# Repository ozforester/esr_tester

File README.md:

# In Circuit ESR Tester
batteries 2xAAA<br>
uc stm32f030f4p6 (cmsis)<br>
opamp mcp6001<br>
switch sn74lvc1g3157dvbr<br>
oled ssd1306 (128x32)<br>
sch and pcb (kicad)<br>

Управляемый делитель операционника для тех,<br>
кто решит экспериментировать с измерением<br>
ёмкости (адаптируя частототу шимов под esr)<br>
Пробная директива сдвига на pi/2 между сигналами<br>
(без адаптации) в главном заголовочном файле<br> 
todo проверка конденсатора на кз

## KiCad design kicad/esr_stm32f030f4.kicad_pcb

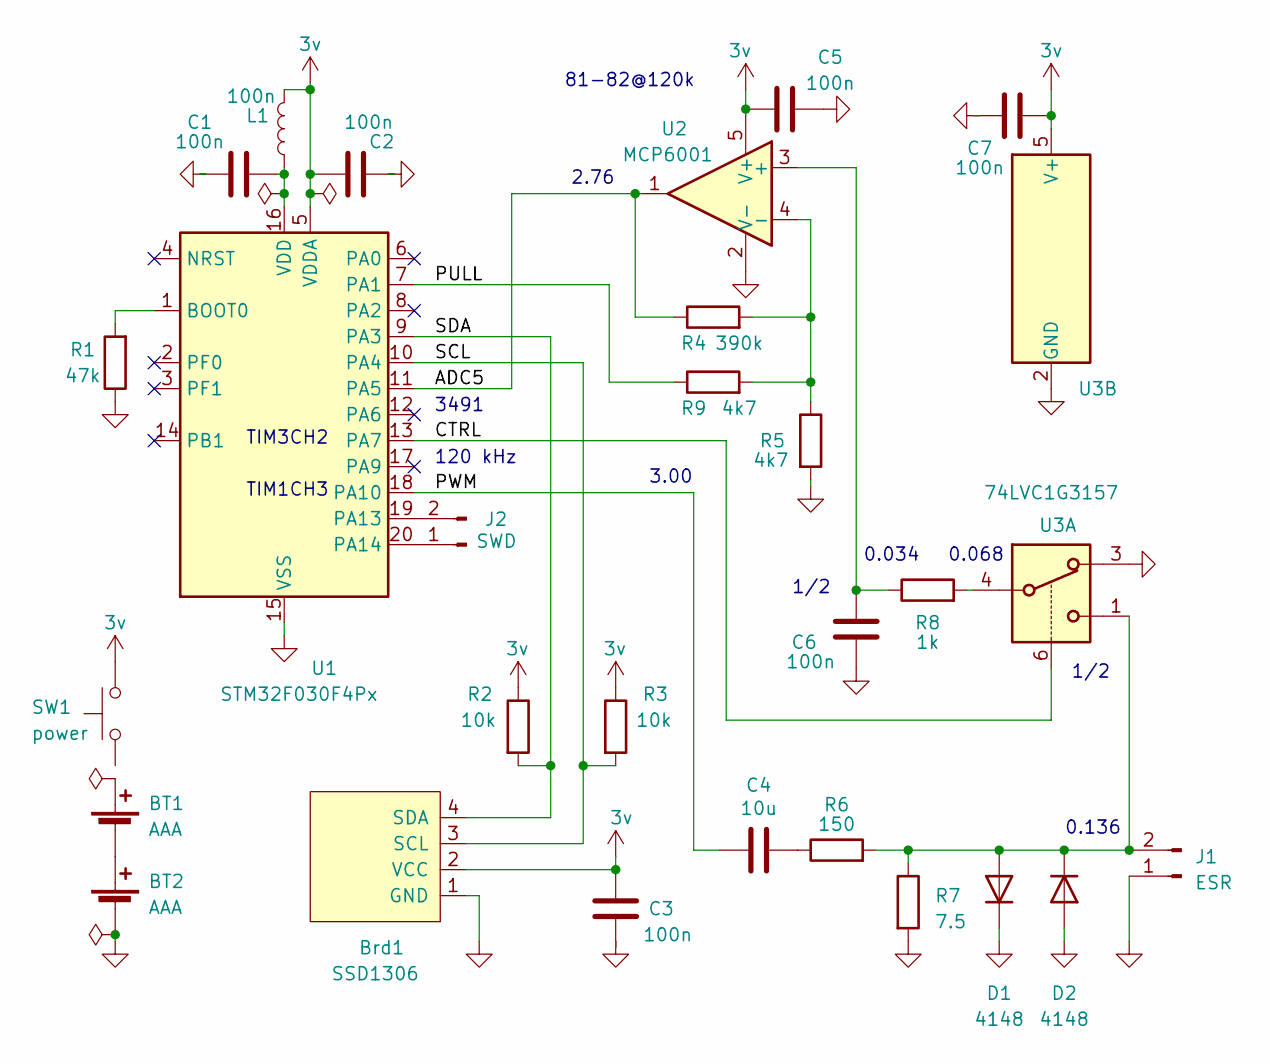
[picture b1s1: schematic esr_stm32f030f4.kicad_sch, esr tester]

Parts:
BT1, BT2: AAA; BatteryHolder_Keystone_2460_1xAA
Brd1: SSD1306; PinHeader_1x04_P2.54mm_Vertical
C1, C2, C3, C5, C6, C7: 100n; C_0805_2012Metric
C4: 10u; C_0805_2012Metric
D1, D2: 4148; D_MiniMELF
J1: ESR; PinHeader_1x02_P2.54mm_Vertical
J2: SWD; PinHeader_1x02_P2.54mm_Vertical
L1: 100n; L_0805_2012Metric
R1: 47k; R_0805_2012Metric
R2, R3: 10k; R_0805_2012Metric
R4: 390k; R_0805_2012Metric
R5, R9: 4k7; R_0805_2012Metric
R6: 150; R_0805_2012Metric
R7: 7.5; R_0805_2012Metric
R8: 1k; R_0805_2012Metric
SW1: power; SW_PUSH_6mm_H5mm
U1: STM32F030F4Px; TSSOP-20_4.4x6.5mm_P0.65mm
U2: MCP6001; SOT-23-5
U3: 74LVC1G3157; SOT-23-6

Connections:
/ADC5: R4.1, U1.11 (PA5), U2.1
/CTRL: U1.13 (PA7), U3.6; also elsewhere on the board
/PWM: C4.2, U1.18 (PA10)
/SCL: Brd1.3 (SCL), R3.2, U1.10 (PA4)
/SDA: Brd1.4 (SDA), R2.2, U1.9 (PA3)
/SHUNT: R9.1, U1.7 (PA1)
GND: BT2.2 (-), Brd1.1 (GND), C1.2, C2.1, C3.1, C5.2, C6.2, C7.2, D1.1 (K), D2.2 (A), J1.1, R1.1, R5.2, R7.2, U1.15 (VSS), U2.2 (V-), U3.2 (GND), U3.3
unnamed: BT1.1 (+), SW1.1
unnamed: BT1.2 (-), BT2.1 (+)
unnamed: C4.1, R6.1
unnamed: D1.2 (A), D2.1 (K), J1.2, R6.2, R7.1, U3.1
unnamed: J2.1, U1.20 (PA14)
unnamed: J2.2, U1.19 (PA13)
unnamed: R8.2, U3.4
unnamed: R1.2, U1.1 (BOOT0)
unnamed: C1.1, L1.1, U1.16 (VDD)
unnamed: C6.1, R8.1, U2.3 (+)
unnamed: R4.2, R5.1, R9.2, U2.4 (-)
VCC: Brd1.2 (VCC), C2.2, C3.2, C5.1, C7.1, L1.2, R2.1, R3.1, SW1.2, U1.5 (VDDA), U2.5 (V+), U3.5 (V+)

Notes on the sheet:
1/2
120 kHz
0.034
2.76
0.136
3491
3.00
TIM3CH2
81-82@120k
TIM1CH3
0.068

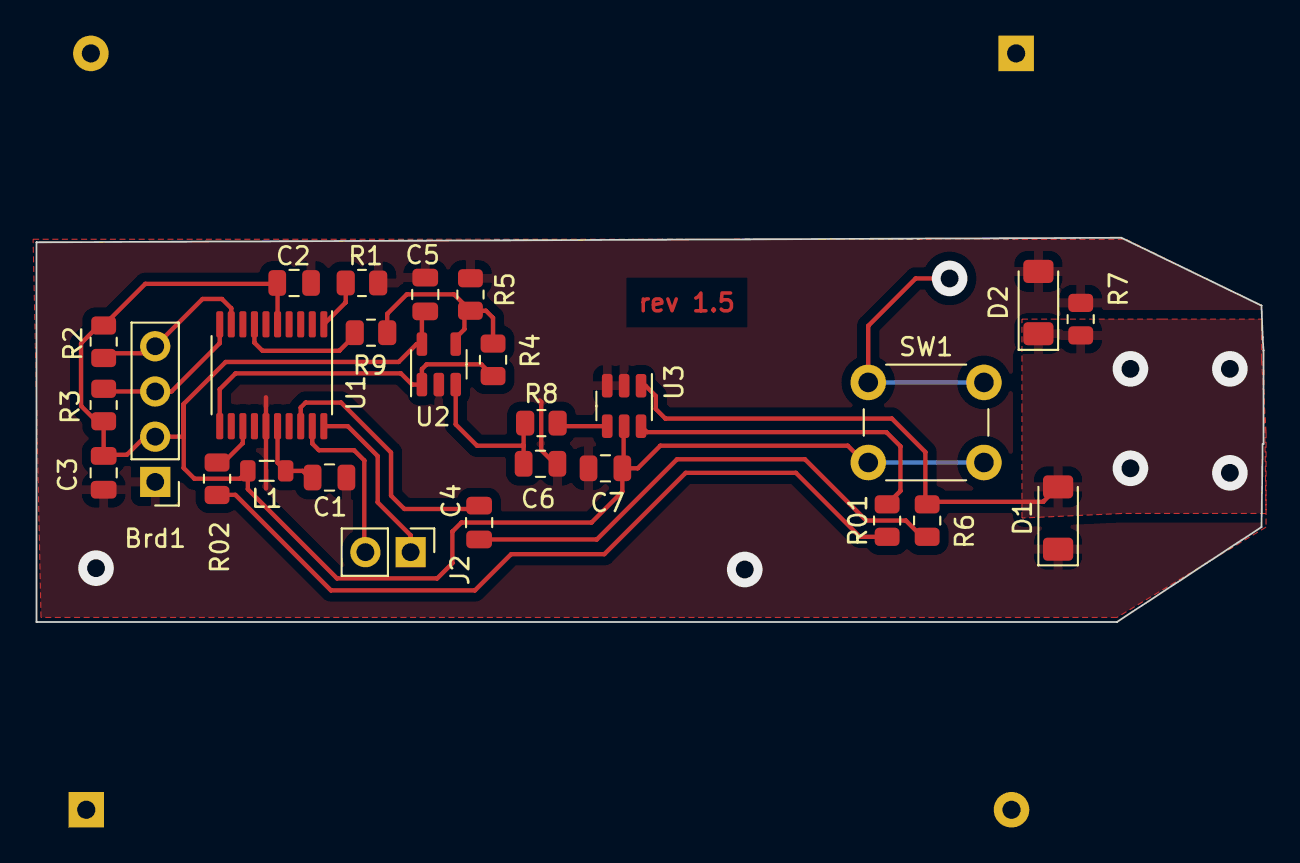
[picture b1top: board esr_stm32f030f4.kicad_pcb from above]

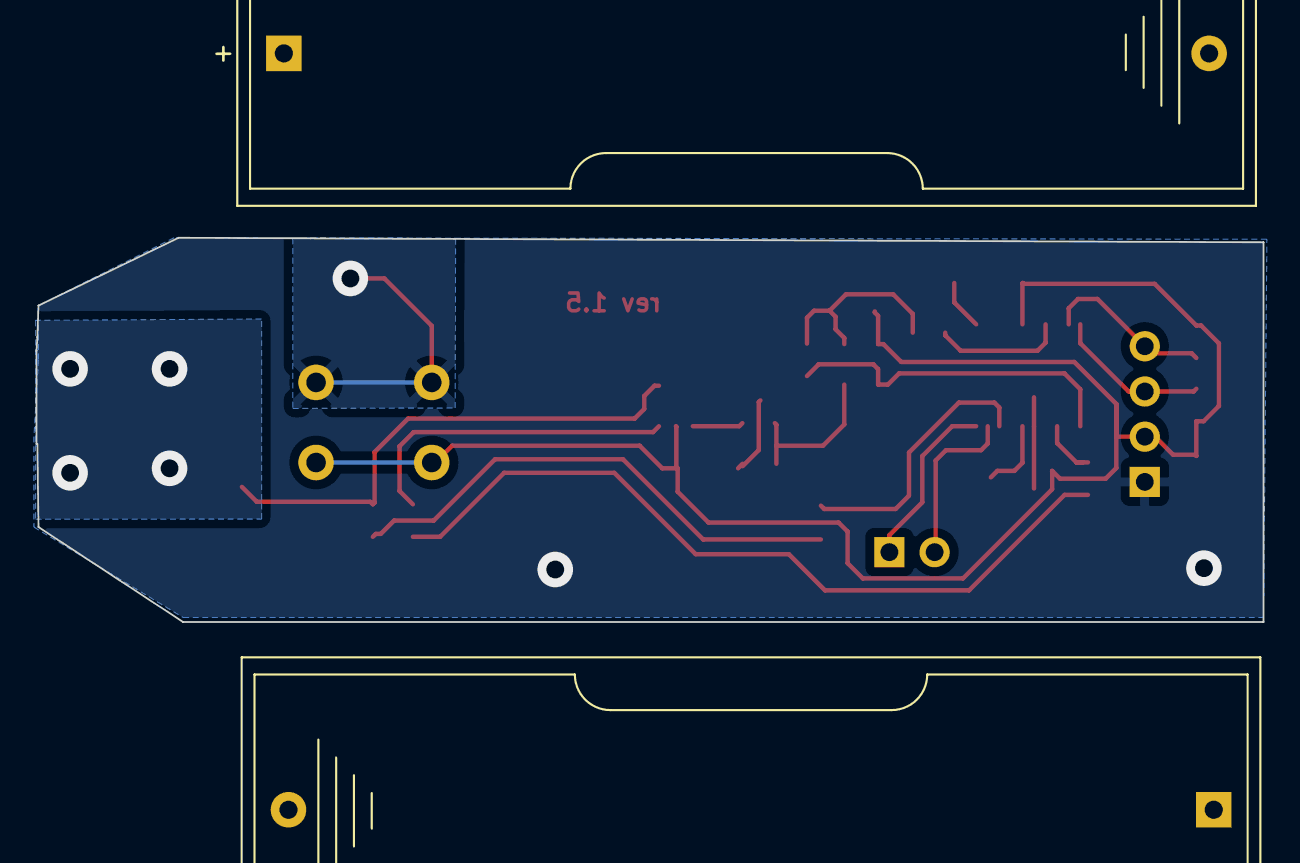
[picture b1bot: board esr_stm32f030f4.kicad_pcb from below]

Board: 2 copper layers, 68.9 x 21.6 mm, 29 parts (2 on the bottom side), 19 nets.

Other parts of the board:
R01, R02: 0; R_0805_2012Metric

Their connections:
/CTRL: R01.1, R01.2, R02.1, R02.2; also elsewhere on the board

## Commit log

2024-09-02 new repo
2025-03-04 init
2025-03-04 pict
2025-03-04 mspl
2025-03-04 add sch
2025-03-04 sch added
2025-03-04 remark
2025-03-04 build
2025-03-05 minor changes
2025-03-12 add pictures
2025-03-12 text
2025-03-12 test
2025-06-15 testing

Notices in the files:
kicad/esr_stm32f030f4.kicad_pcb:
CC-BY-SA 4.0 License
